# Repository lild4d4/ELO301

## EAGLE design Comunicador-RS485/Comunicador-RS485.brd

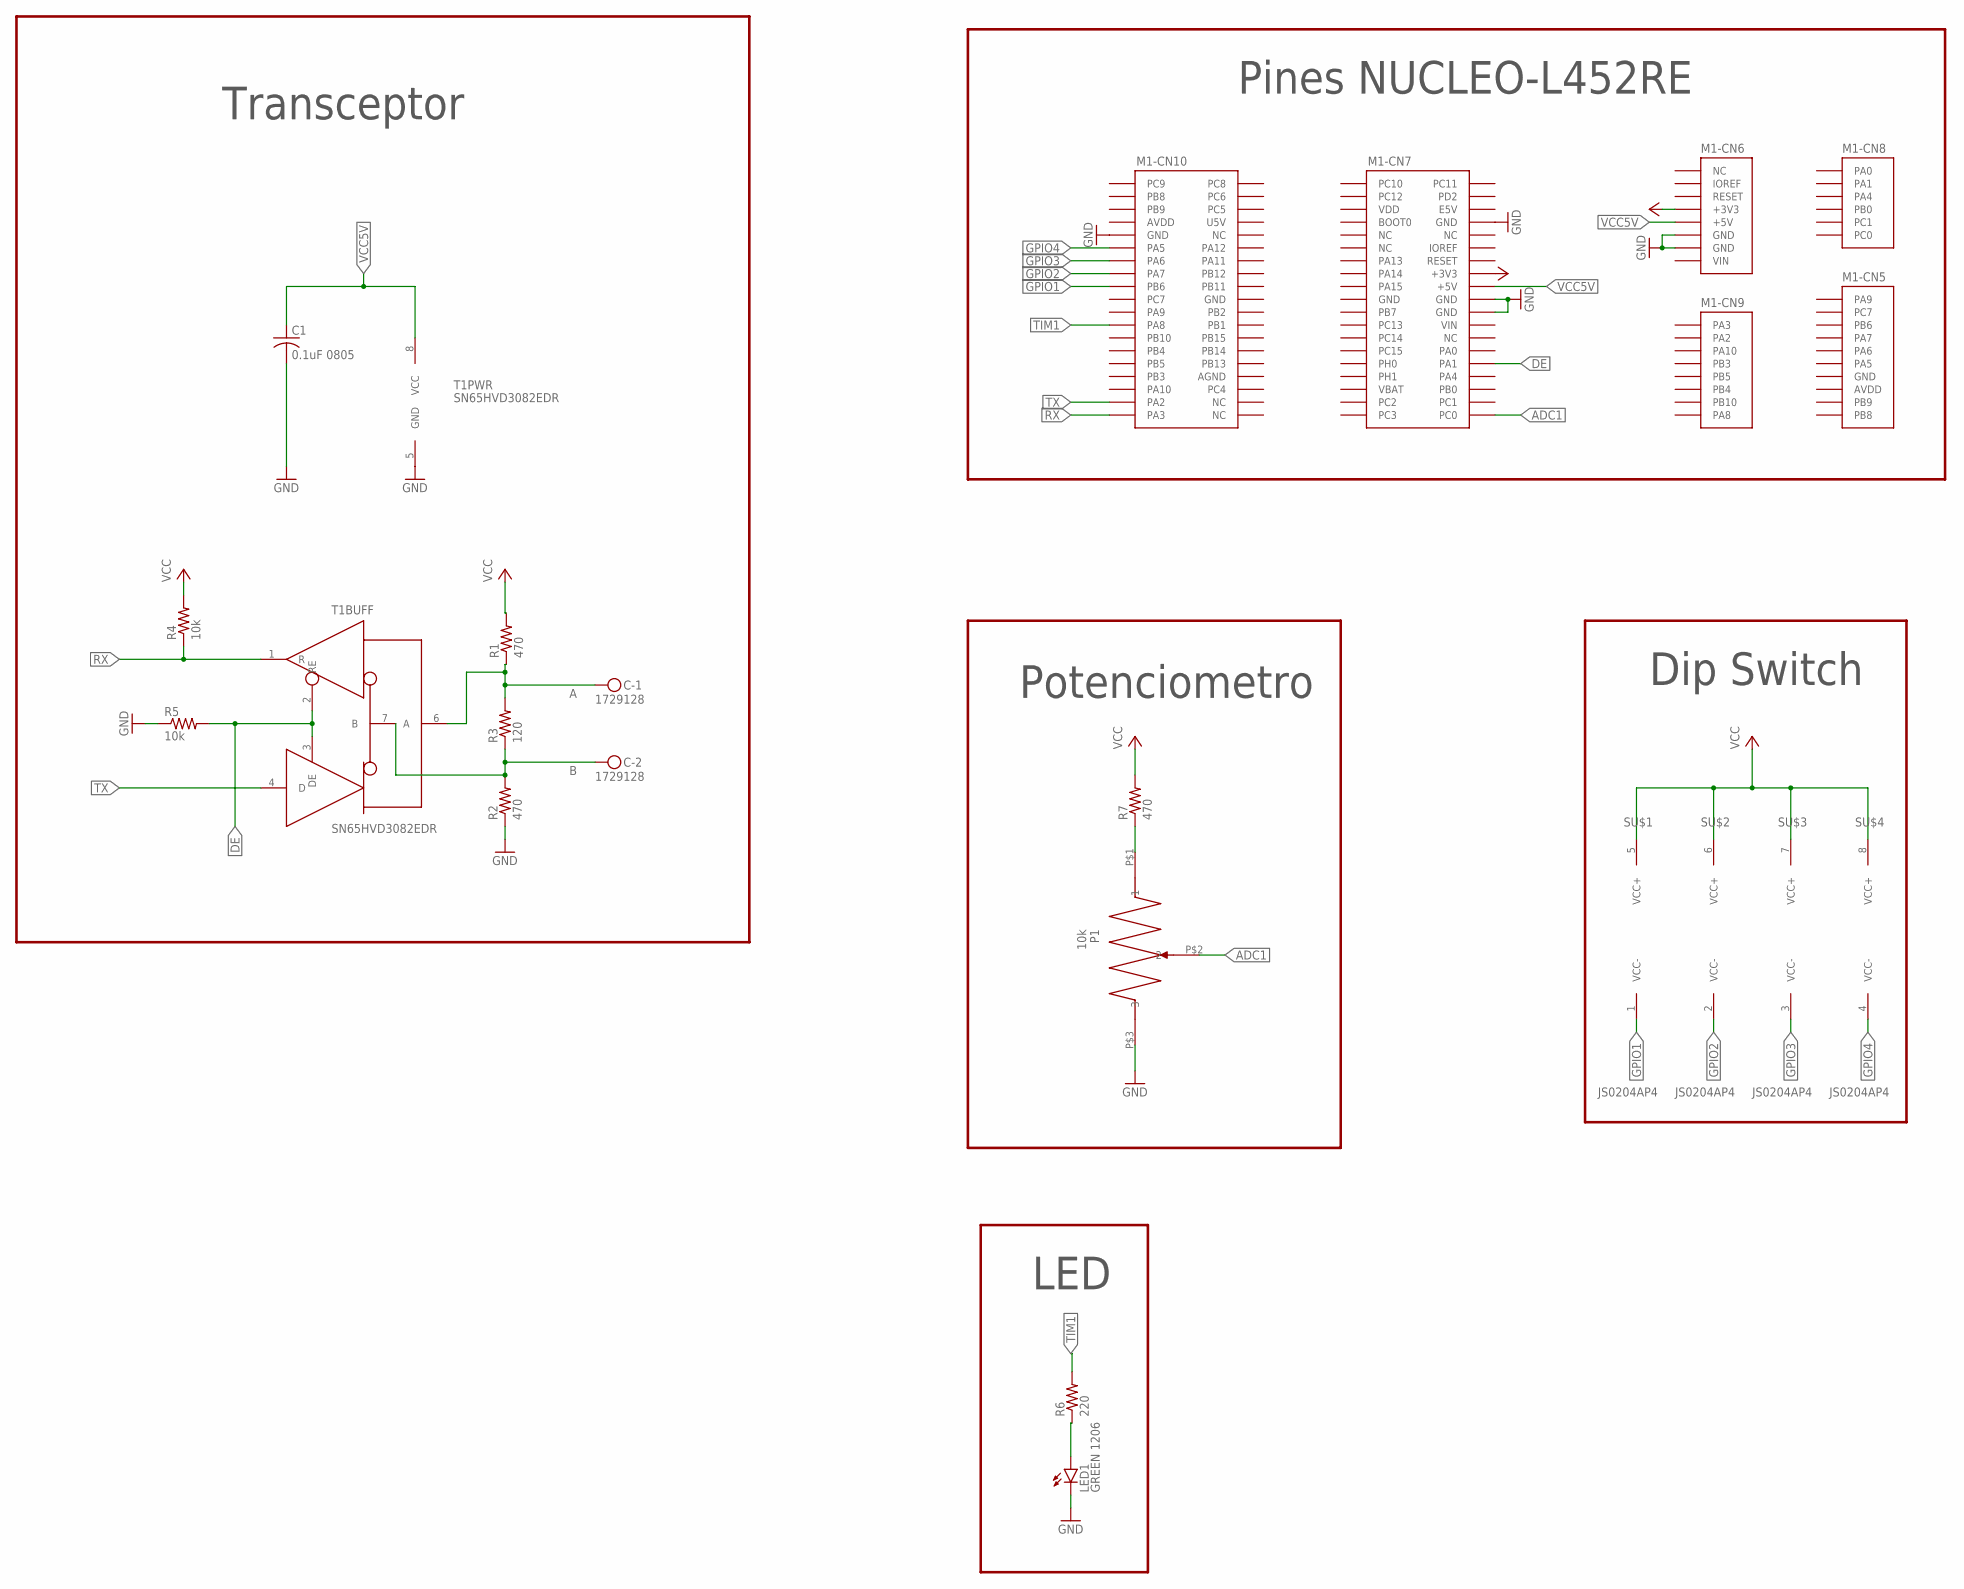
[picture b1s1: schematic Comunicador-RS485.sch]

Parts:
C: 1729128; MKDSN1,5/2-5,08; PARTNO 1729128
C1: 0.1uF 0805; C0805; PARTNO 08053C104KAT2A
LED1: GREEN 1206; CHIPLED_1206; PARTNO CMD15-21VGD/TR8
M1: NUCLEO-L452RE; NUCLEO-64
P1: 10k; PTV09A-4; PARTNO PTV09A-4015U-B103
R1, R2, R7: 470; R0805; PARTNO AC0805FR-07470RL
R3: 120; R0805; PARTNO RC0805JR-13120RL
R4, R5: 10k; R0805; PARTNO RC0805FR-0710KP
R6: 220; R0805; PARTNO AC0805FR-07220RL
S: JS0204AP4; JS0204AP; PARTNO JS0204AP4
T1: SN65HVD3082EDR; 8-SOIC; PARTNO SN65HVD3082EDR

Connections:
A: C.1, R1.1, R3.2, T1.6 (A)
ADC1: M1.CN7-38 (PC0), P1.P$2 (2)
AGND: M1.CN10-32 (AGND)
AVDD: M1.CN5-8 (AVDD), M1.CN10-7 (AVDD)
B: C.2, R2.2, R3.1, T1.7 (B)
DE: M1.CN7-30 (PA1), R5.2, T1.2 (RE), T1.3 (DE)
GND: C1.2, LED1.C, M1.CN5-7 (GND), M1.CN6-6 (GND), M1.CN6-7 (GND), M1.CN7-8 (GND), M1.CN7-19 (GND), M1.CN7-20 (GND), M1.CN7-22 (GND), M1.CN10-9 (GND), M1.CN10-20 (GND), P1.P$3 (3), R2.1, R5.1, T1.5 (GND)
GPIO1: M1.CN10-17 (PB6), S.1 (VCC-)
GPIO2: M1.CN10-15 (PA7), S.2 (VCC-)
GPIO3: M1.CN10-13 (PA6), S.3 (VCC-)
GPIO4: M1.CN10-11 (PA5), S.4 (VCC-)
IOREF: M1.CN6-2 (IOREF)
unnamed: LED1.A, R6.1
unnamed: P1.P$1 (1), R7.1
RX: M1.CN10-37 (PA3), R4.1, T1.1 (R)
TIM1: M1.CN10-23 (PA8), R6.2
TX: M1.CN10-35 (PA2), T1.4 (D)
U5V: M1.CN10-8 (U5V)
VBAT: M1.CN7-33 (VBAT)
VCC: M1.CN6-4 (+3V3), M1.CN7-16 (+3V3), R1.2, R4.2, R7.2, S.5 (VCC+), S.6 (VCC+), S.7 (VCC+), S.8 (VCC+)
VCC5V: C1.1, M1.CN6-5 (+5V), M1.CN7-18 (+5V), T1.8 (VCC)
VDD: M1.CN7-5 (VDD)
VIN: M1.CN6-8 (VIN), M1.CN7-24 (VIN)

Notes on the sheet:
Pines NUCLEO-L452RE
Transceptor
Dip Switch
Potenciometro
LED

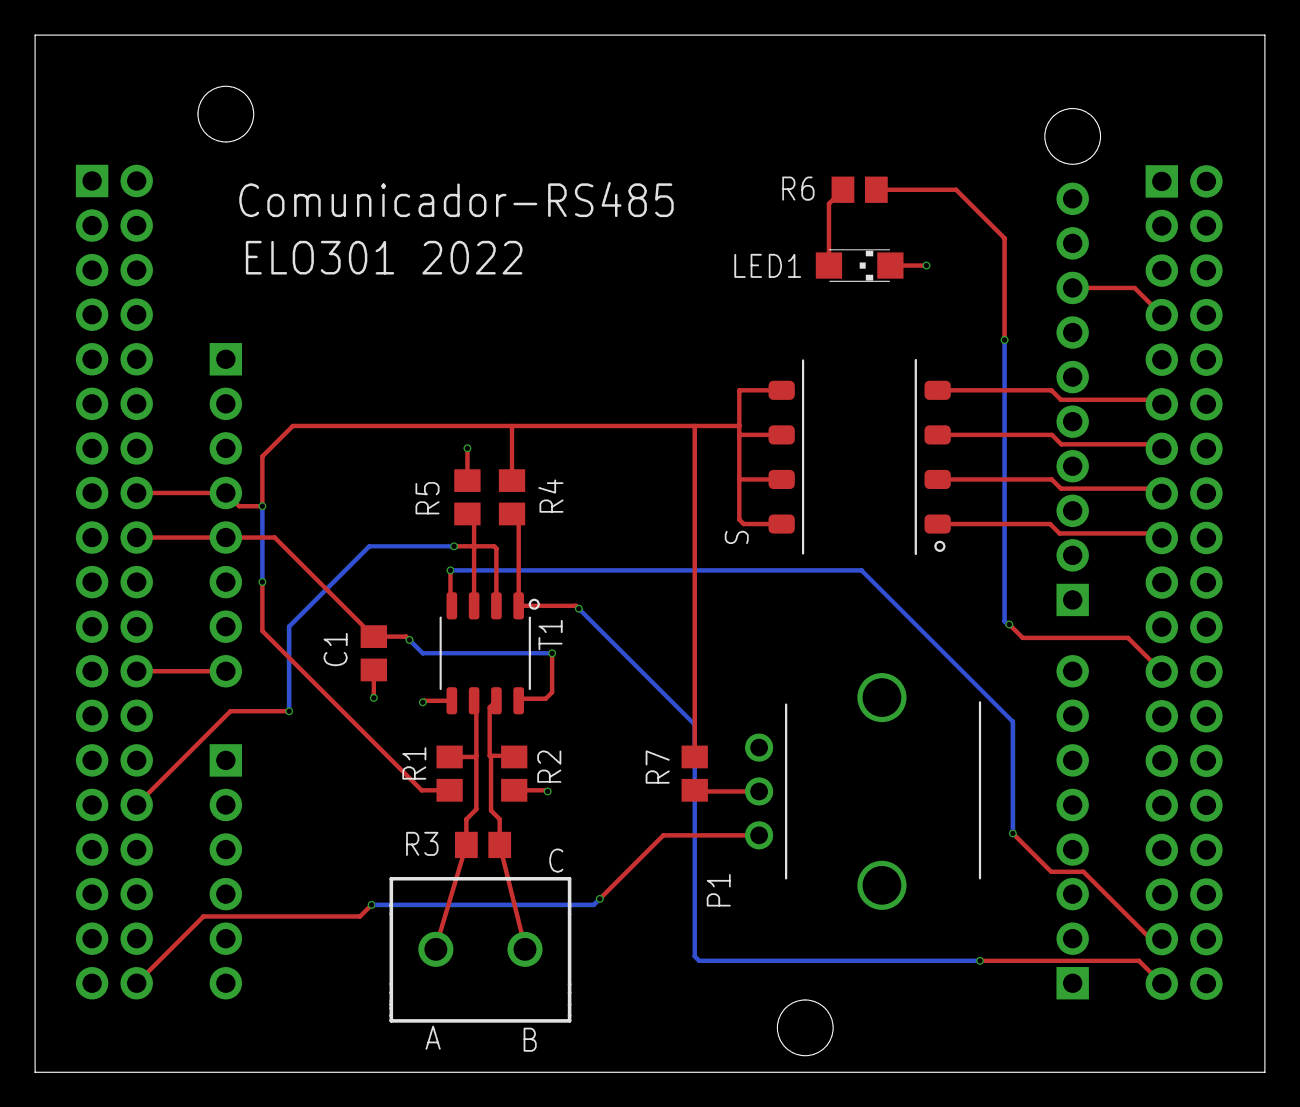
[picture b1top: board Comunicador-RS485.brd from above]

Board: 2 copper layers, 70.1 x 59.1 mm, 14 parts (0 on the bottom side), 18 nets.

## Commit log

2022-11-17 se agrego partnumber nucleo
2022-12-06 firmware initial commit
2022-12-06 se agregó la libreria commando_decoder
2022-12-06 (re)implementado el UART a poto pelao
    hola
2022-12-08 ultimo update del firmware
    alo
2022-12-08 no + errores
2022-12-08 arreglao this_device
2022-12-09 todo funciona TODO
    incluso el timer guiño
2022-12-10 no se que son estas weas tbh
    a
2022-12-11 se agrego libreria potenciometro
2022-12-11 estructs
2022-12-12 se agrego libreria led
2022-12-13 doxygen
2022-12-14 usart1 a uart4
2022-12-14 usart1 a uart4 parte 2
2022-12-15 ultimos changes ulala
2022-12-16 todo listoco barroco
2022-12-16 todo pero todo todo listo
    si se pudo burro
2022-12-16 (me falto algo en el doxygen)
    jeje
2022-12-16 y este archivo jaj
2022-12-16 final final final ahora si
